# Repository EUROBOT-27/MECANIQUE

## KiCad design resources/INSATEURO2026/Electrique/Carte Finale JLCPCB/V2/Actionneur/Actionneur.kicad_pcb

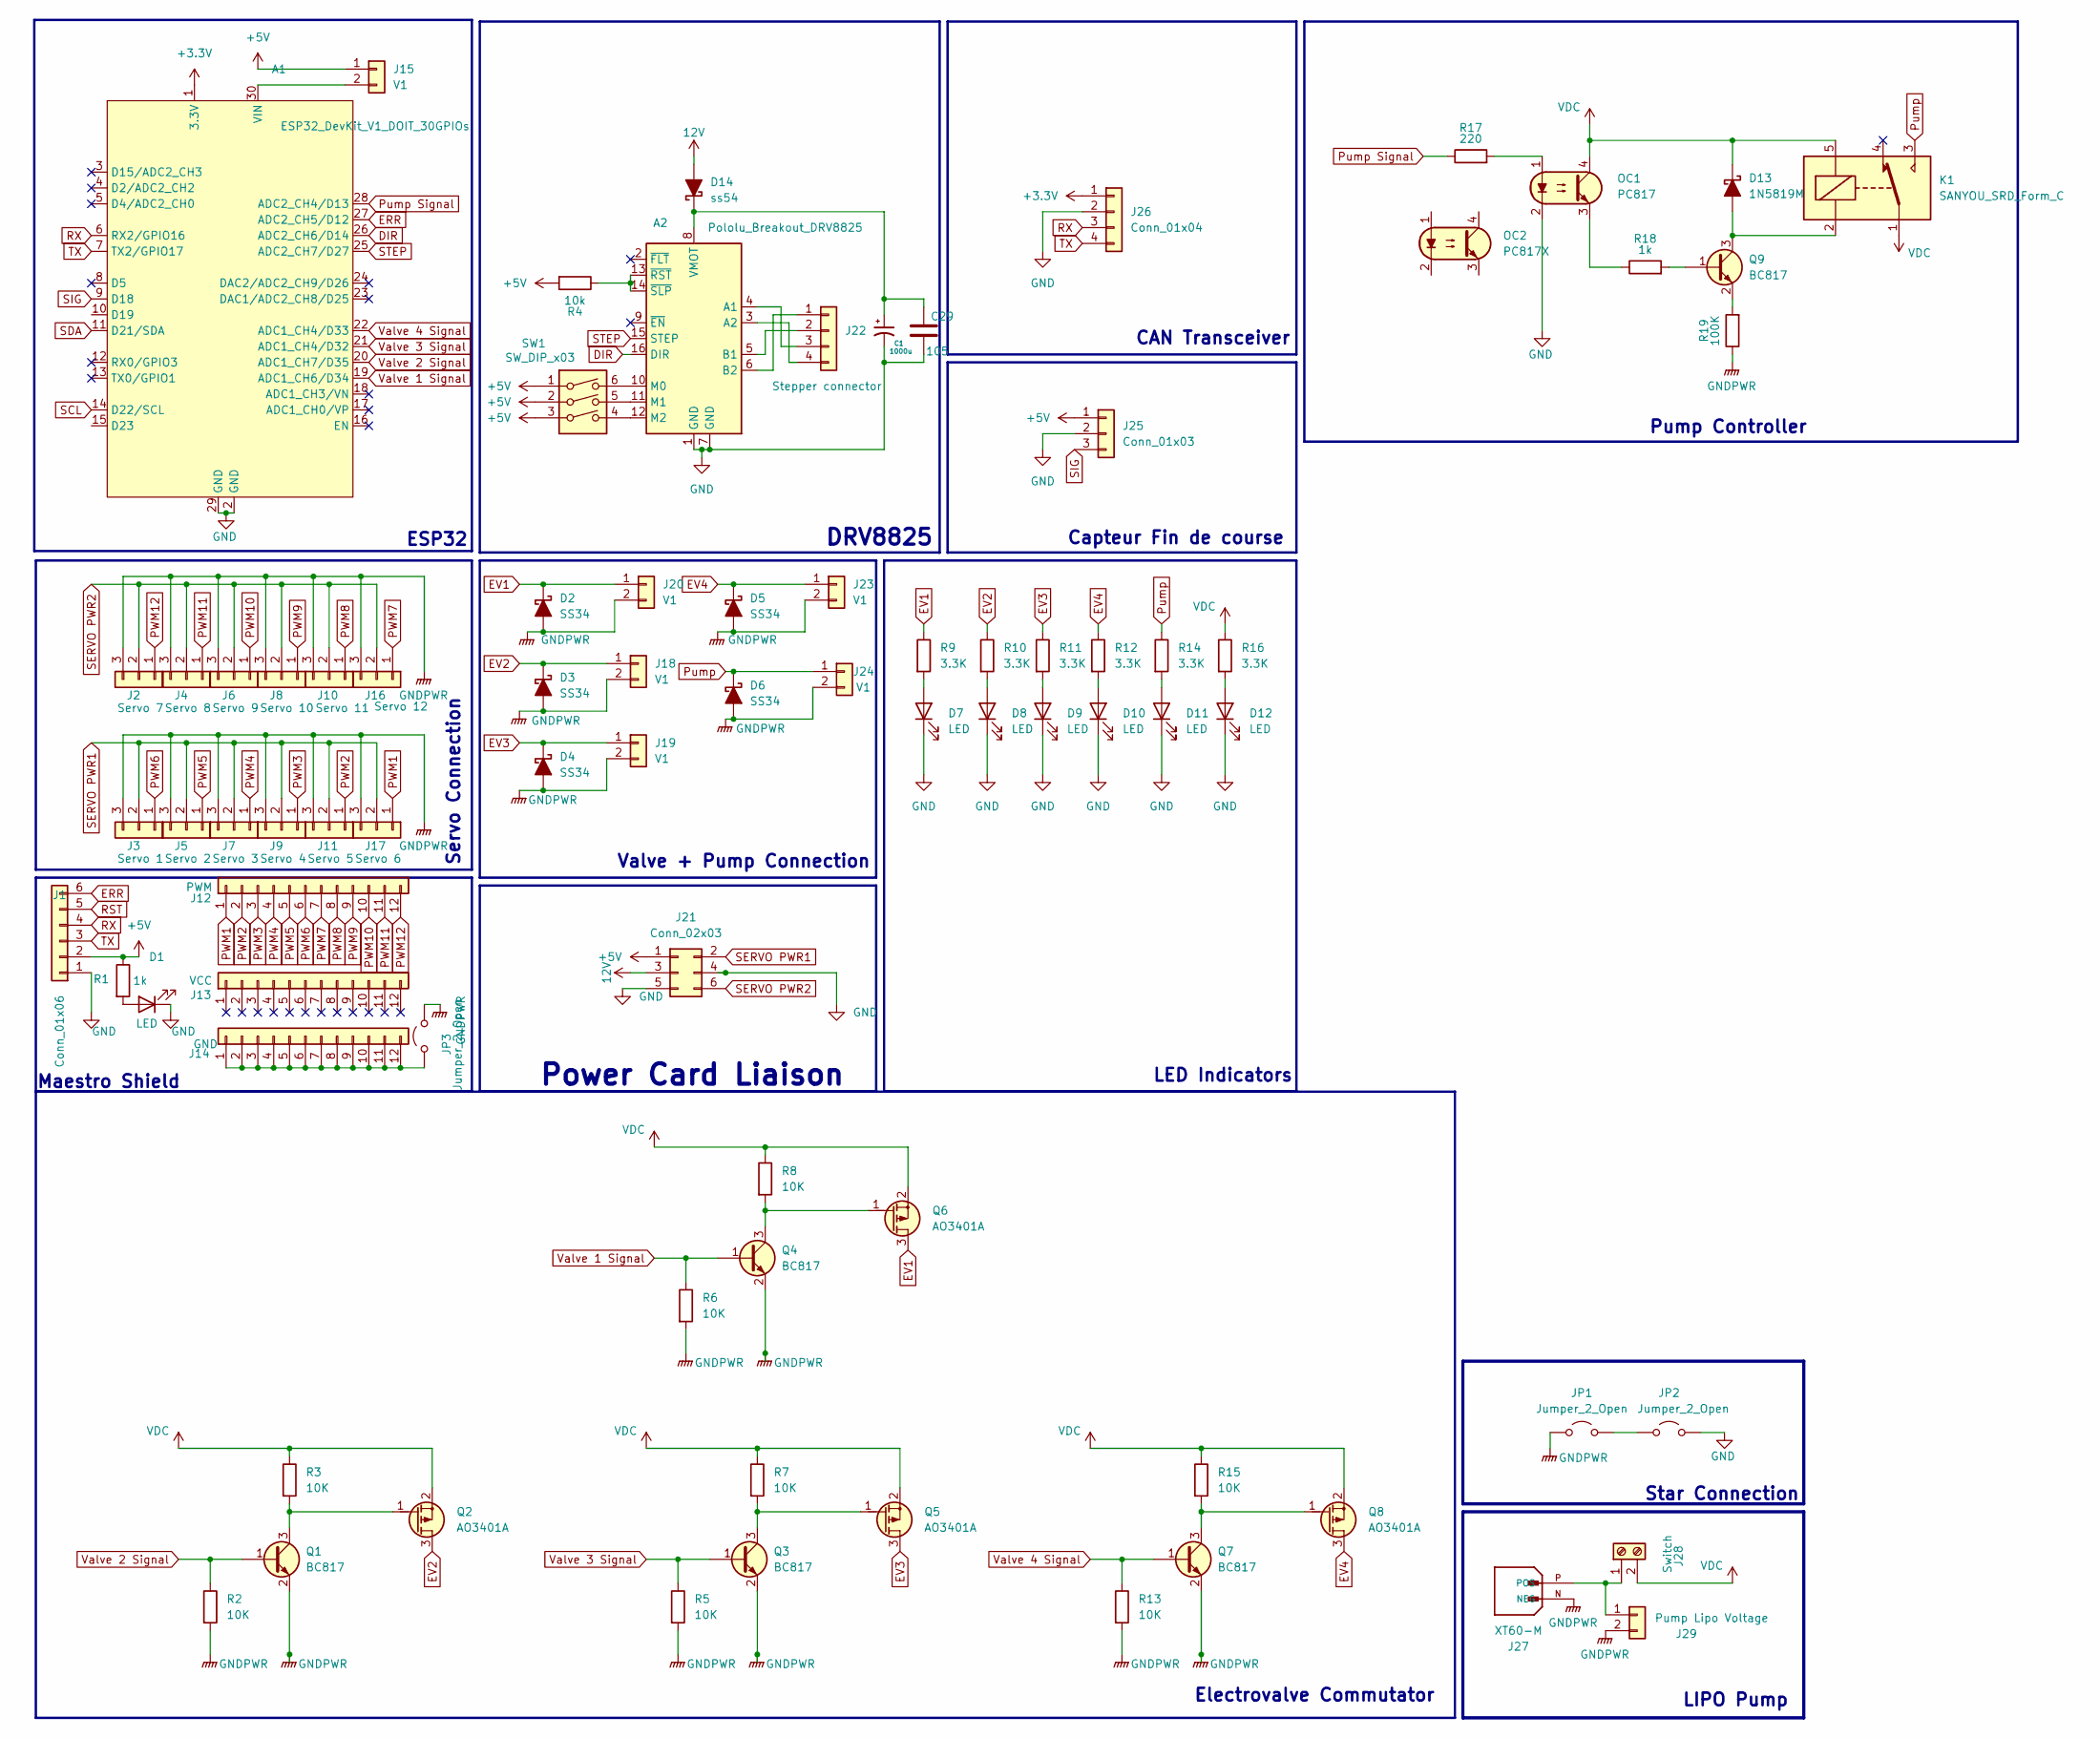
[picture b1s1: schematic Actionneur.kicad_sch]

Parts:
A1: ESP32_DevKit_V1_DOIT_30GPIOs; DOIT_ESP32_DEVKIT_30Pins
A2: Pololu_Breakout_DRV8825; Pololu_Breakout-16_15.2x20.3mm
C1: 1000u; CP_Elec_10x10.5
C29: 105; C_0603_1608Metric
D1, D7, D8, D9, D10, D11, D12: LED; LED_0603_1608Metric
D2, D3, D4, D5, D6: SS34; D_SOD-323
D13: 1N5819M; D_SMC
D14: ss54; D_SOD-323
J1: Conn_01x06; PinSocket_1x06_P2.54mm_Vertical
J2: Servo 7; PinHeader_1x03_P2.54mm_Vertical
J3: Servo 1; PinHeader_1x03_P2.54mm_Vertical
J4: Servo 8; PinHeader_1x03_P2.54mm_Vertical
J5: Servo 2; PinHeader_1x03_P2.54mm_Vertical
J6: Servo 9; PinHeader_1x03_P2.54mm_Vertical
J7: Servo 3; PinHeader_1x03_P2.54mm_Vertical
J8: Servo 10; PinHeader_1x03_P2.54mm_Vertical
J9: Servo 4; PinHeader_1x03_P2.54mm_Vertical
J10: Servo 11; PinHeader_1x03_P2.54mm_Vertical
J11: Servo 5; PinHeader_1x03_P2.54mm_Vertical
J12: PWM; PinSocket_1x12_P2.54mm_Vertical
J13: VCC; PinSocket_1x12_P2.54mm_Vertical
J14: GND; PinSocket_1x12_P2.54mm_Vertical
J15, J18, J19, J20, J23, J24: V1; JST_PH_B2B-PH-K_1x02_P2.00mm_Vertical
J16: Servo 12; PinHeader_1x03_P2.54mm_Vertical
J17: Servo 6; PinHeader_1x03_P2.54mm_Vertical
J21: Conn_02x03; Molex_Mini-Fit_Jr_5566-06A_2x03_P4.20mm_Vertical
J22: Stepper connector; JST_EH_B4B-EH-A_1x04_P2.50mm_Vertical
J25: Conn_01x03; JST_EH_B3B-EH-A_1x03_P2.50mm_Vertical
J26: Conn_01x04; JST_EH_B4B-EH-A_1x04_P2.50mm_Vertical
J27: XT60-M; AMASS_XT60-M; PARTREV V1.2
J28: Switch; TerminalBlock_Phoenix_MKDS-1,5-2-5.08_1x02_P5.08mm_Horizont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
J29: Pump Lipo Voltage; JST_PH_B2B-PH-K_1x02_P2.00mm_Vertical
JP1, JP2, JP3: Jumper_2_Open; Jumper_P2.54mm_D0.7mm
K1: SANYOU_SRD_Form_C; Relay_SPDT_SANYOU_SRD_Series_Form_C
OC1: PC817; Vishay_CNY64
OC2: PC817X; DIP-4_W7.62mm_LongPads
Q1, Q3, Q4, Q7, Q9: BC817; SOT-23
Q2, Q5, Q6, Q8: AO3401A; SOT-23
R1, R18: 1k; R_0603_1608Metric
R2, R3, R5, R6, R7, R8, R13, R15: 10K; R_0603_1608Metric
R4: 10k; R_0603_1608Metric
R9, R10, R11, R12, R14, R16: 3.3K; R_0603_1608Metric
R17: 220; R_0603_1608Metric
R19: 100K; R_0603_1608Metric
SW1: SW_DIP_x03; SW_DIP_SPSTx03_Slide_6.7x9.18mm_W6.73mm_P2.54mm_LowProfile_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

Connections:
12V: D14.2 (A), J21.3
+3.3V: A1.1 (3.3V), J26.1
+5V: J1.2, J15.1, J21.1, J25.1, R1.1, R4.2, SW1.1, SW1.2, SW1.3
Alt Pump: K1.4
DIR: A1.26 (ADC2_CH6/D14), A2.16 (DIR)
ERR: A1.27 (ADC2_CH5/D12), J1.6
EV1: D2.1 (K), J20.1, Q6.3 (D), R9.1
EV2: D3.1 (K), J18.1, Q2.3 (D), R10.1
EV3: D4.1 (K), J19.1, Q5.3 (D), R11.1
EV4: D5.1 (K), J23.1, Q8.3 (D), R12.1
GND: A1.2 (GND), A1.29 (GND), A2.1 (GND), A2.7 (GND), C1.2, C29.2, D1.1 (K), D7.1 (K), D8.1 (K), D9.1 (K), D10.1 (K), D11.1 (K), D12.1 (K), J1.1, J21.4, J21.5, J25.2, J26.2, JP2.2 (B), OC1.2
GNDPWR: D2.2 (A), D3.2 (A), D4.2 (A), D5.2 (A), D6.2 (A), J2.3, J3.3, J4.3, J5.3, J6.3, J7.3, J8.3, J9.3, J10.3, J11.3, J16.3, J17.3, J18.2, J19.2, J20.2, J23.2, J24.2, J27.N (NEG), J29.2, JP1.1 (A), JP3.2 (B), Q1.2 (E), Q3.2 (E), Q4.2 (E), Q7.2 (E), R2.2, R5.2, R6.2, R13.2, R19.1
unnamed: A1.30 (VIN), J15.2
unnamed: A2.4 (A1), J22.3
unnamed: A2.3 (A2), J22.4
unnamed: A2.5 (B1), J22.2
unnamed: A2.6 (B2), J22.1
unnamed: A2.10 (M0), SW1.6
unnamed: A2.11 (M1), SW1.5
unnamed: A2.12 (M2), SW1.4
unnamed: A2.8 (VMOT), C1.1, C29.1, D14.1 (K)
unnamed: A2.13 (~RST), A2.14 (~SLP), R4.1
unnamed: D1.2 (A), R1.2
unnamed: D7.2 (A), R9.2
unnamed: D8.2 (A), R10.2
unnamed: D9.2 (A), R11.2
unnamed: D10.2 (A), R12.2
unnamed: D11.2 (A), R14.2
unnamed: D12.2 (A), R16.2
unnamed: D13.2 (A), K1.2, Q9.3 (C)
unnamed: J14.1, J14.2, J14.3, J14.4, J14.5, J14.6, J14.7, J14.8, J14.9, J14.10, J14.11, J14.12, JP3.1 (A)
unnamed: J27.P (POS), J28.1, J29.1
unnamed: JP1.2 (B), JP2.1 (A)
unnamed: OC1.1, R17.2
unnamed: OC1.3, R18.1
unnamed: Q1.3 (C), Q2.1 (G), R3.2
unnamed: Q3.3 (C), Q5.1 (G), R7.2
unnamed: Q4.3 (C), Q6.1 (G), R8.2
unnamed: Q7.3 (C), Q8.1 (G), R15.2
unnamed: Q9.1 (B), R18.2
unnamed: Q9.2 (E), R19.2
PWM1: J12.1, J17.1
PWM2: J11.1, J12.2
PWM3: J9.1, J12.3
PWM4: J7.1, J12.4
PWM5: J5.1, J12.5
PWM6: J3.1, J12.6
PWM7: J12.7, J16.1
PWM8: J10.1, J12.8
PWM9: J8.1, J12.9
PWM10: J6.1, J12.10
PWM11: J4.1, J12.11
PWM12: J2.1, J12.12
Pump: D6.1 (K), J24.1, K1.3, R14.1
Pump Signal: A1.28 (ADC2_CH4/D13), R17.1
RST: J1.5
RX: A1.6 (RX2/GPIO16), J1.4, J26.3
SCL: A1.14 (D22/SCL)
SDA: A1.11 (D21/SDA)
SERVO PWR1: J3.2, J5.2, J7.2, J9.2, J11.2, J17.2, J21.2
SERVO PWR2: J2.2, J4.2, J6.2, J8.2, J10.2, J16.2, J21.6
SIG: A1.9 (D18), J25.3
STEP: A1.25 (ADC2_CH7/D27), A2.15 (STEP)
TX: A1.7 (TX2/GPIO17), J1.3, J26.4
VDC: D13.1 (K), J28.2, K1.1, K1.5, OC1.4, Q2.2 (S), Q5.2 (S), Q6.2 (S), Q8.2 (S), R3.1, R7.1, R8.1, R15.1, R16.1
Valve 1 Signal: A1.19 (ADC1_CH6/D34), Q4.1 (B), R6.1
Valve 2 Signal: A1.20 (ADC1_CH7/D35), Q1.1 (B), R2.1
Valve 3 Signal: A1.21 (ADC1_CH4/D32), Q3.1 (B), R5.1
Valve 4 Signal: A1.22 (ADC1_CH4/D33), Q7.1 (B), R13.1

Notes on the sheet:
LED Indicators
ESP32
LIPO Pump
Valve + Pump Connection
Star Connection
CAN Transceiver
Maestro Shield
Electrovalve Commutator
DRV8825
Pump Controller
Power Card Liaison
Servo Connection
Capteur Fin de course

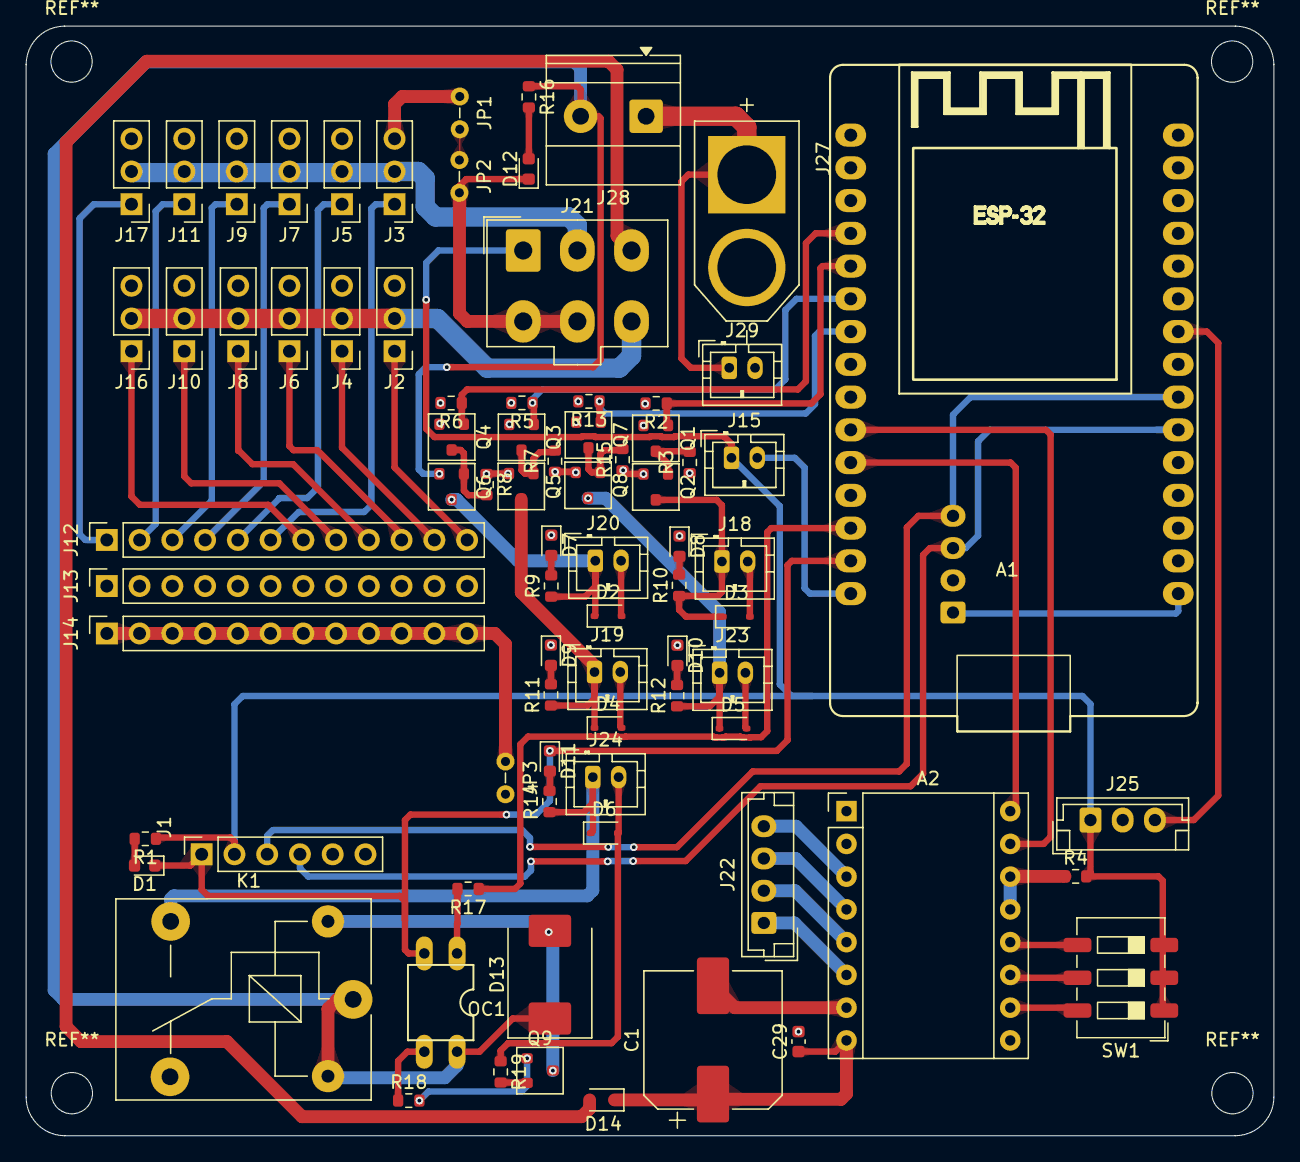
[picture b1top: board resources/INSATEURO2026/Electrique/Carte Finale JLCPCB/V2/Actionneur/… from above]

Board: 4 copper layers, 96.8 x 86.1 mm, 81 parts (1 on the bottom side), 65 nets.

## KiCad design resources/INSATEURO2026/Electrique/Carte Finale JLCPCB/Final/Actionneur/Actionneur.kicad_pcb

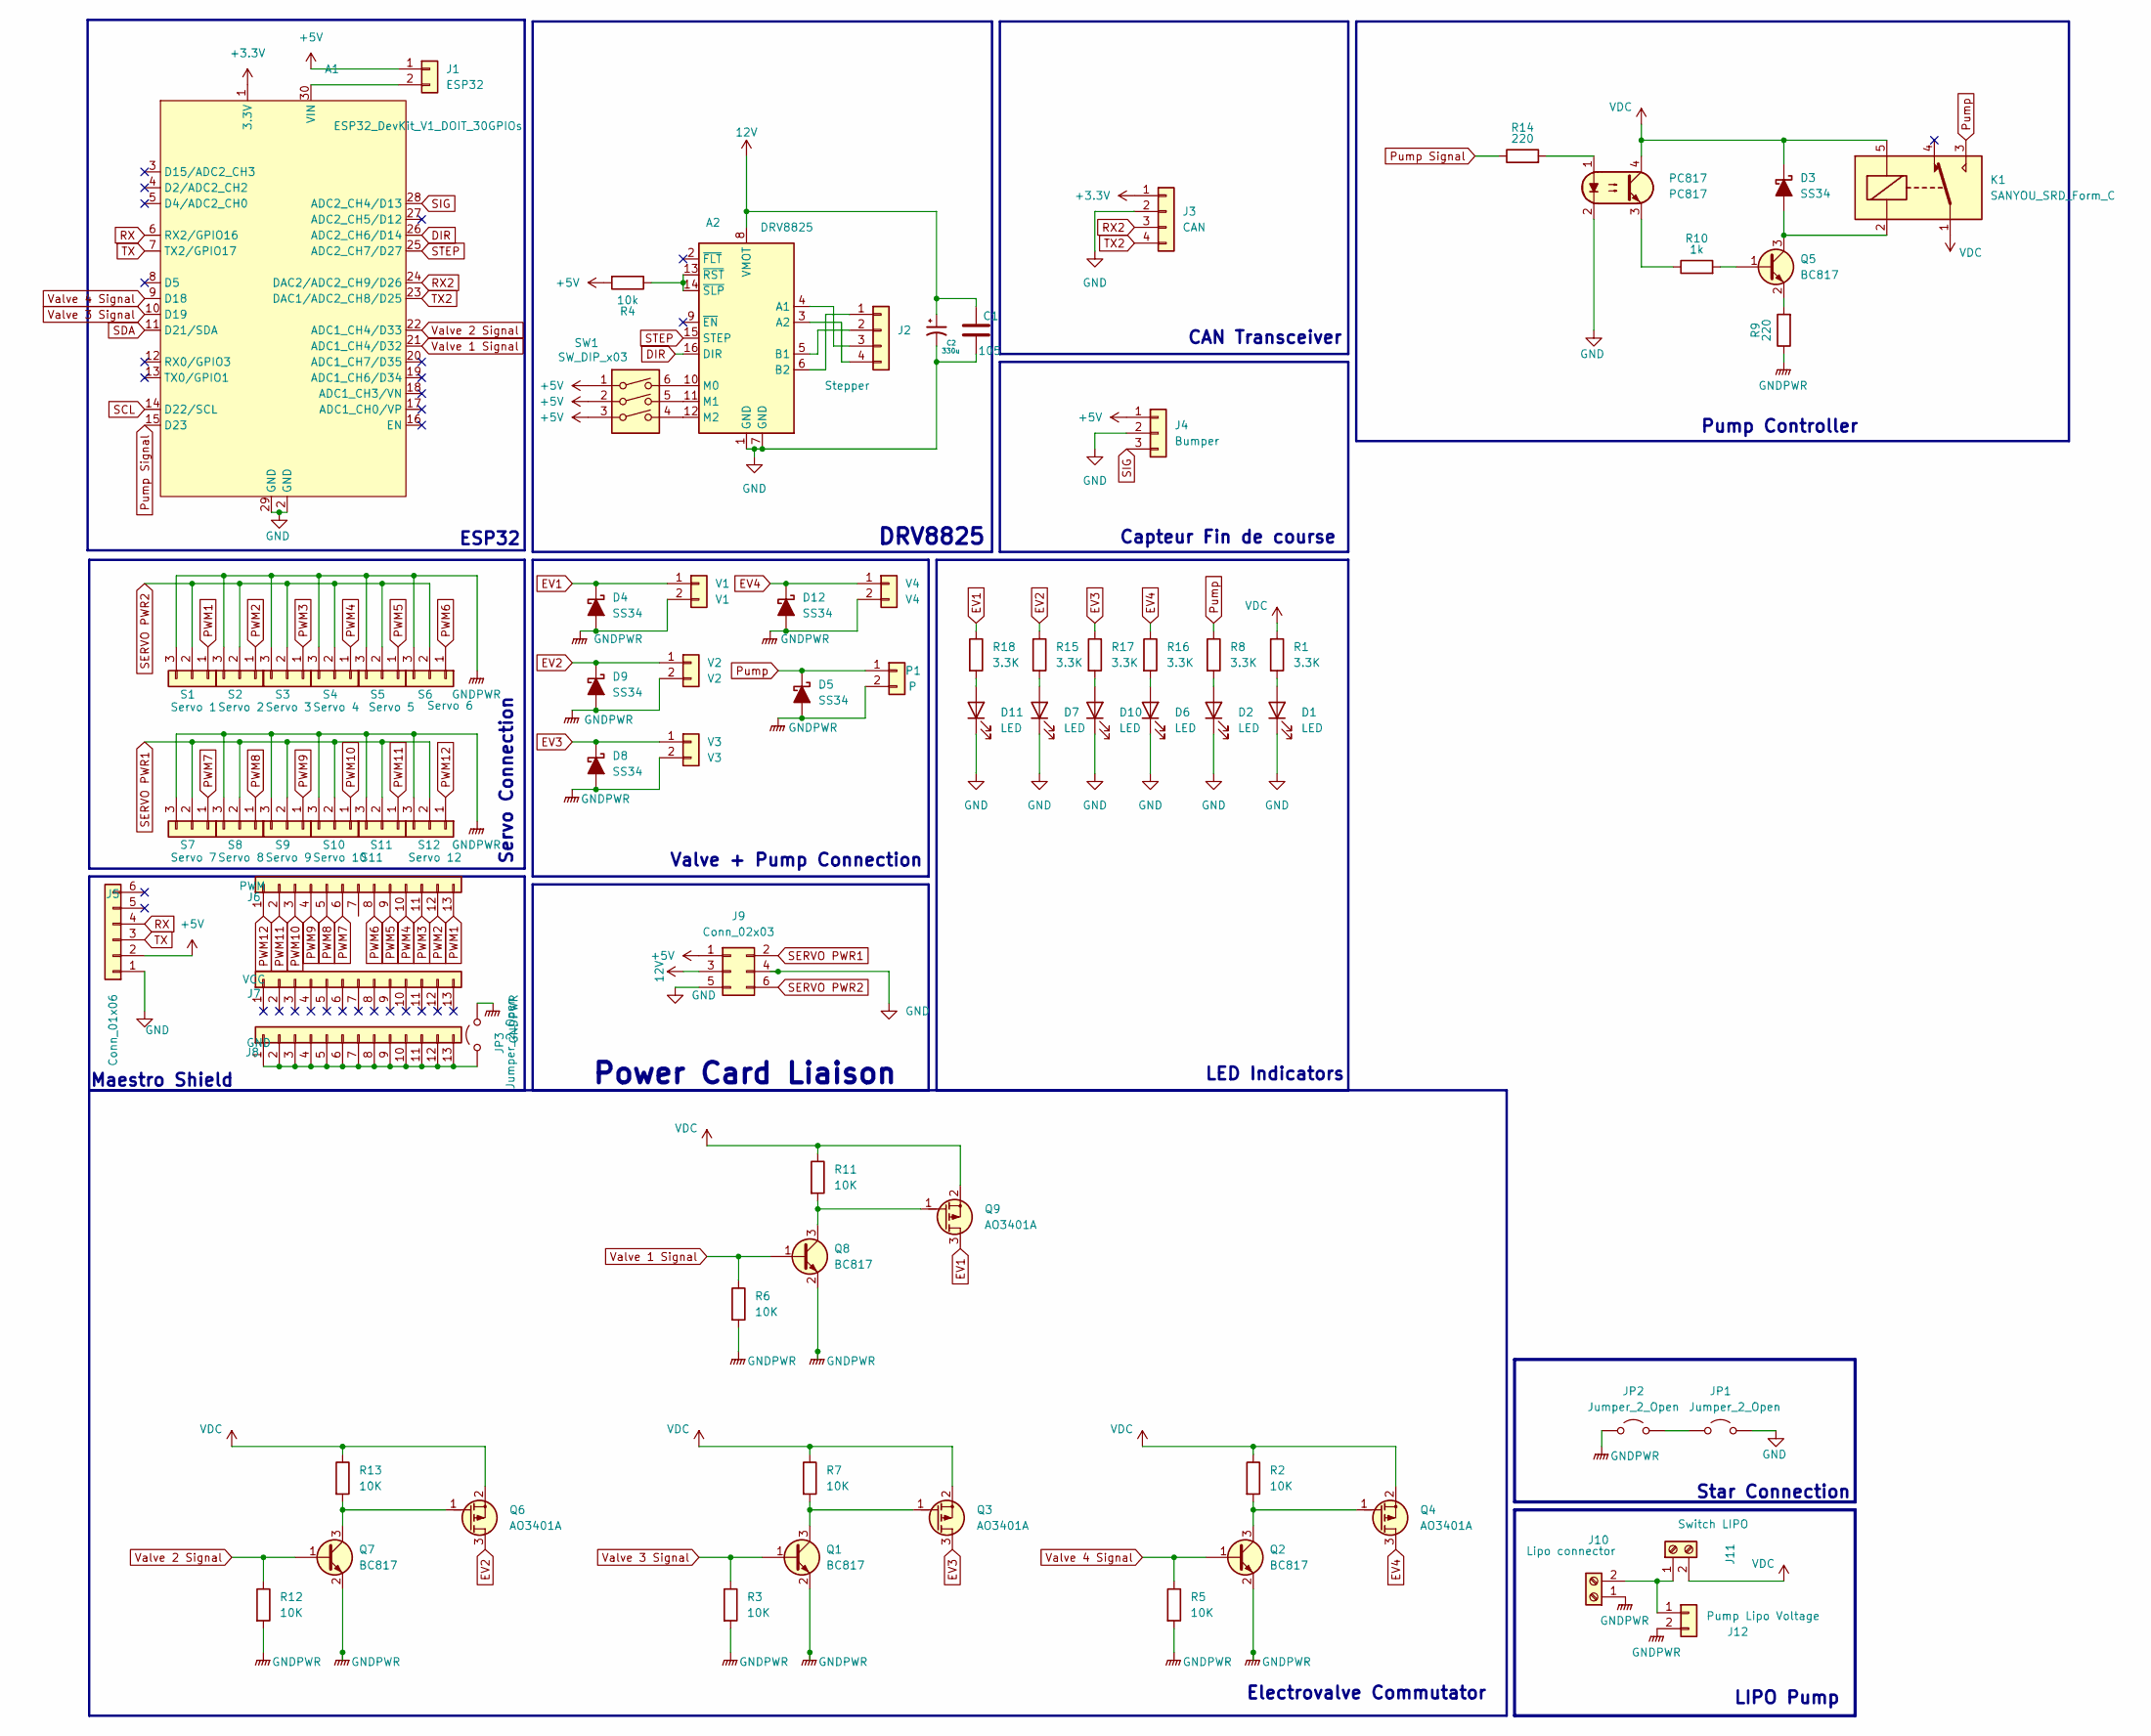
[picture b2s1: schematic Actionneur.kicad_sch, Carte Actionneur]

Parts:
A1: ESP32_DevKit_V1_DOIT_30GPIOs; DOIT_ESP32_DEVKIT_30Pins
A2: DRV8825; Pololu_Breakout-16_15.2x20.3mm
C1: 105; C_0603_1608Metric
C2: 330u; CP_Elec_10x10.5
D1, D2, D6, D7, D10, D11: LED; LED_0603_1608Metric
D3, D4, D5, D8, D9, D12: SS34; D_SOD-323
J1: ESP32; JST_XH_B2B-XH-A_1x02_P2.50mm_Vertical
J2: Stepper; JST_EH_B4B-EH-A_1x04_P2.50mm_Vertical
J3: CAN; JST_EH_B4B-EH-A_1x04_P2.50mm_Vertical
J4: Bumper; JST_EH_B3B-EH-A_1x03_P2.50mm_Vertical
J5: Conn_01x06; PinSocket_1x06_P2.54mm_Vertical
J6: PWM; PinSocket_1x13_P2.54mm_Vertical
J7: VCC; PinSocket_1x13_P2.54mm_Vertical
J8: GND; PinSocket_1x13_P2.54mm_Vertical
J9: Conn_02x03; Molex_Mini-Fit_Jr_5566-06A_2x03_P4.20mm_Vertical
J10: Lipo connector; TerminalBlock_Phoenix_MKDS-1,5-2-5.08_1x02_P5.08mm_Horizont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
J11: Switch LIPO; TerminalBlock_Phoenix_MKDS-1,5-2-5.08_1x02_P5.08mm_Horizont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
J12: Pump Lipo Voltage; JST_PH_B2B-PH-K_1x02_P2.00mm_Vertical
JP1, JP3: Jumper_2_Open; TestPoint_2Pads_Pitch2.54mm_Drill0.8mm
JP2: Jumper_2_Open; Jumper_P2.54mm_D0.7mm
K1: SANYOU_SRD_Form_C; Relay_SPDT_SANYOU_SRD_Series_Form_C
P1: P; JST_PH_B2B-PH-K_1x02_P2.00mm_Vertical
PC817: PC817; DIP-4_W7.62mm
Q1, Q2, Q5, Q7, Q8: BC817; SOT-23
Q3, Q4, Q6, Q9: AO3401A; SOT-23
R1, R8, R15, R16, R17, R18: 3.3K; R_0603_1608Metric
R2, R3, R5, R6, R7, R11, R12, R13: 10K; R_0603_1608Metric
R4: 10k; R_0603_1608Metric
R9, R14: 220; R_0603_1608Metric
R10: 1k; R_0603_1608Metric
S1: Servo 1; PinHeader_1x03_P2.54mm_Vertical
S2: Servo 2; PinHeader_1x03_P2.54mm_Vertical
S3: Servo 3; PinHeader_1x03_P2.54mm_Vertical
S4: Servo 4; PinHeader_1x03_P2.54mm_Vertical
S5: Servo 5; PinHeader_1x03_P2.54mm_Vertical
S6: Servo 6; PinHeader_1x03_P2.54mm_Vertical
S7: Servo 7; PinHeader_1x03_P2.54mm_Vertical
S8: Servo 8; PinHeader_1x03_P2.54mm_Vertical
S9: Servo 9; PinHeader_1x03_P2.54mm_Vertical
S10: Servo 10; PinHeader_1x03_P2.54mm_Vertical
S11: S11; PinHeader_1x03_P2.54mm_Vertical
S12: Servo 12; PinHeader_1x03_P2.54mm_Vertical
SW1: SW_DIP_x03; SW_DIP_SPSTx03_Slide_6.7x9.18mm_W6.73mm_P2.54mm_LowProfile_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
V1: V1; JST_PH_B2B-PH-K_1x02_P2.00mm_Vertical
V2: V2; JST_PH_B2B-PH-K_1x02_P2.00mm_Vertical
V3: V3; JST_PH_B2B-PH-K_1x02_P2.00mm_Vertical
V4: V4; JST_PH_B2B-PH-K_1x02_P2.00mm_Vertical

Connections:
12V: A2.8 (VMOT), C1.1, C2.1, J9.3
+3.3V: A1.1 (3.3V), J3.1
+5V: J1.1, J4.1, J5.2, J9.1, R4.2, SW1.1, SW1.2, SW1.3
DIR: A1.26 (ADC2_CH6/D14), A2.16 (DIR)
EV1: D4.1 (K), Q9.3 (D), R18.1, V1.1
EV2: D9.1 (K), Q6.3 (D), R15.1, V2.1
EV3: D8.1 (K), Q3.3 (D), R17.1, V3.1
EV4: D12.1 (K), Q4.3 (D), R16.1, V4.1
GND: A1.2 (GND), A1.29 (GND), A2.1 (GND), A2.7 (GND), C1.2, C2.2, D1.1 (K), D2.1 (K), D6.1 (K), D7.1 (K), D10.1 (K), D11.1 (K), J3.2, J4.2, J5.1, J9.4, J9.5, JP1.2 (B), PC817.2
GNDPWR: D4.2 (A), D5.2 (A), D8.2 (A), D9.2 (A), D12.2 (A), J10.1, J12.2, JP2.1 (A), JP3.2 (B), P1.2, Q1.2 (E), Q2.2 (E), Q7.2 (E), Q8.2 (E), R3.2, R5.2, R6.2, R9.1, R12.2, S1.3, S2.3, S3.3, S4.3, S5.3, S6.3, S7.3, S8.3, S9.3, S10.3, S11.3, S12.3, V1.2, V2.2, V3.2, V4.2
unnamed: A1.30 (VIN), J1.2
unnamed: A2.4 (A1), J2.3
unnamed: A2.3 (A2), J2.4
unnamed: A2.5 (B1), J2.2
unnamed: A2.6 (B2), J2.1
unnamed: A2.10 (M0), SW1.6
unnamed: A2.11 (M1), SW1.5
unnamed: A2.12 (M2), SW1.4
unnamed: A2.13 (~RST), A2.14 (~SLP), R4.1
unnamed: D1.2 (A), R1.2
unnamed: D2.2 (A), R8.2
unnamed: D3.2 (A), K1.2, Q5.3 (C)
unnamed: D6.2 (A), R16.2
unnamed: D7.2 (A), R15.2
unnamed: D10.2 (A), R17.2
unnamed: D11.2 (A), R18.2
unnamed: J8.1, J8.2, J8.3, J8.4, J8.5, J8.6, J8.7, J8.8, J8.9, J8.10, J8.11, J8.12, J8.13, JP3.1 (A)
unnamed: J10.2, J11.1, J12.1
unnamed: JP1.1 (A), JP2.2 (B)
unnamed: PC817.1, R14.2
unnamed: PC817.3, R10.1
unnamed: Q1.3 (C), Q3.1 (G), R7.2
unnamed: Q2.3 (C), Q4.1 (G), R2.2
unnamed: Q5.1 (B), R10.2
unnamed: Q5.2 (E), R9.2
unnamed: Q6.1 (G), Q7.3 (C), R13.2
unnamed: Q8.3 (C), Q9.1 (G), R11.2
PWM1: J6.13, S1.1
PWM2: J6.12, S2.1
PWM3: J6.11, S3.1
PWM4: J6.10, S4.1
PWM5: J6.9, S5.1
PWM6: J6.8, S6.1
PWM7: J6.6, S7.1
PWM8: J6.5, S8.1
PWM9: J6.4, S9.1
PWM10: J6.3, S10.1
PWM11: J6.2, S11.1
PWM12: J6.1, S12.1
Pump: D5.1 (K), K1.3, P1.1, R8.1
Pump Signal: A1.15 (D23), R14.1
RX: A1.6 (RX2/GPIO16), J5.4
RX2: A1.24 (DAC2/ADC2_CH9/D26), J3.3
SCL: A1.14 (D22/SCL)
SDA: A1.11 (D21/SDA)
SERVO PWR1: J9.2, S7.2, S8.2, S9.2, S10.2, S11.2, S12.2
SERVO PWR2: J9.6, S1.2, S2.2, S3.2, S4.2, S5.2, S6.2
SIG: A1.28 (ADC2_CH4/D13), J4.3
STEP: A1.25 (ADC2_CH7/D27), A2.15 (STEP)
TX: A1.7 (TX2/GPIO17), J5.3
TX2: A1.23 (DAC1/ADC2_CH8/D25), J3.4
VDC: D3.1 (K), J11.2, K1.1, K1.5, PC817.4, Q3.2 (S), Q4.2 (S), Q6.2 (S), Q9.2 (S), R1.1, R2.1, R7.1, R11.1, R13.1
Valve 1 Signal: A1.21 (ADC1_CH4/D32), Q8.1 (B), R6.1
Valve 2 Signal: A1.22 (ADC1_CH4/D33), Q7.1 (B), R12.1
Valve 3 Signal: A1.10 (D19), Q1.1 (B), R3.1
Valve 4 Signal: A1.9 (D18), Q2.1 (B), R5.1

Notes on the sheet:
LED Indicators
ESP32
LIPO Pump
Valve + Pump Connection
Star Connection
CAN Transceiver
Maestro Shield
Electrovalve Commutator
DRV8825
Pump Controller
Power Card Liaison
Servo Connection
Capteur Fin de course

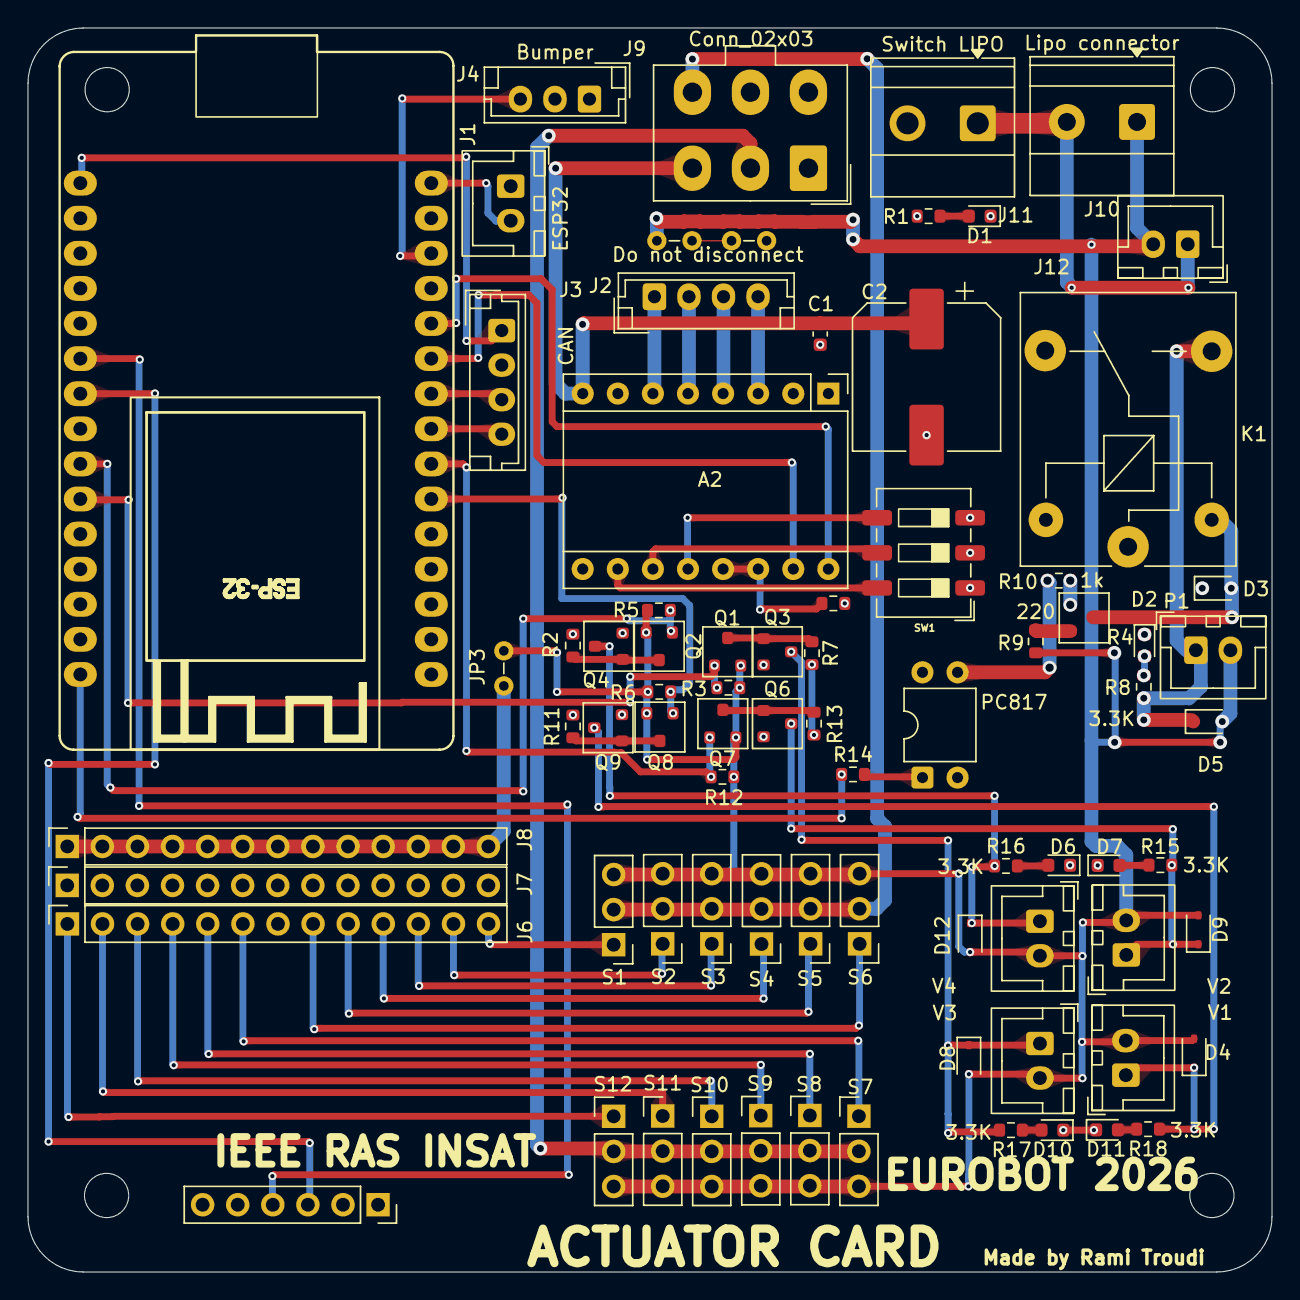
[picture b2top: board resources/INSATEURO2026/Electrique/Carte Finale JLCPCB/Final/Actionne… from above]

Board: 4 copper layers, 90.0 x 90.0 mm, 78 parts (0 on the bottom side), 64 nets.

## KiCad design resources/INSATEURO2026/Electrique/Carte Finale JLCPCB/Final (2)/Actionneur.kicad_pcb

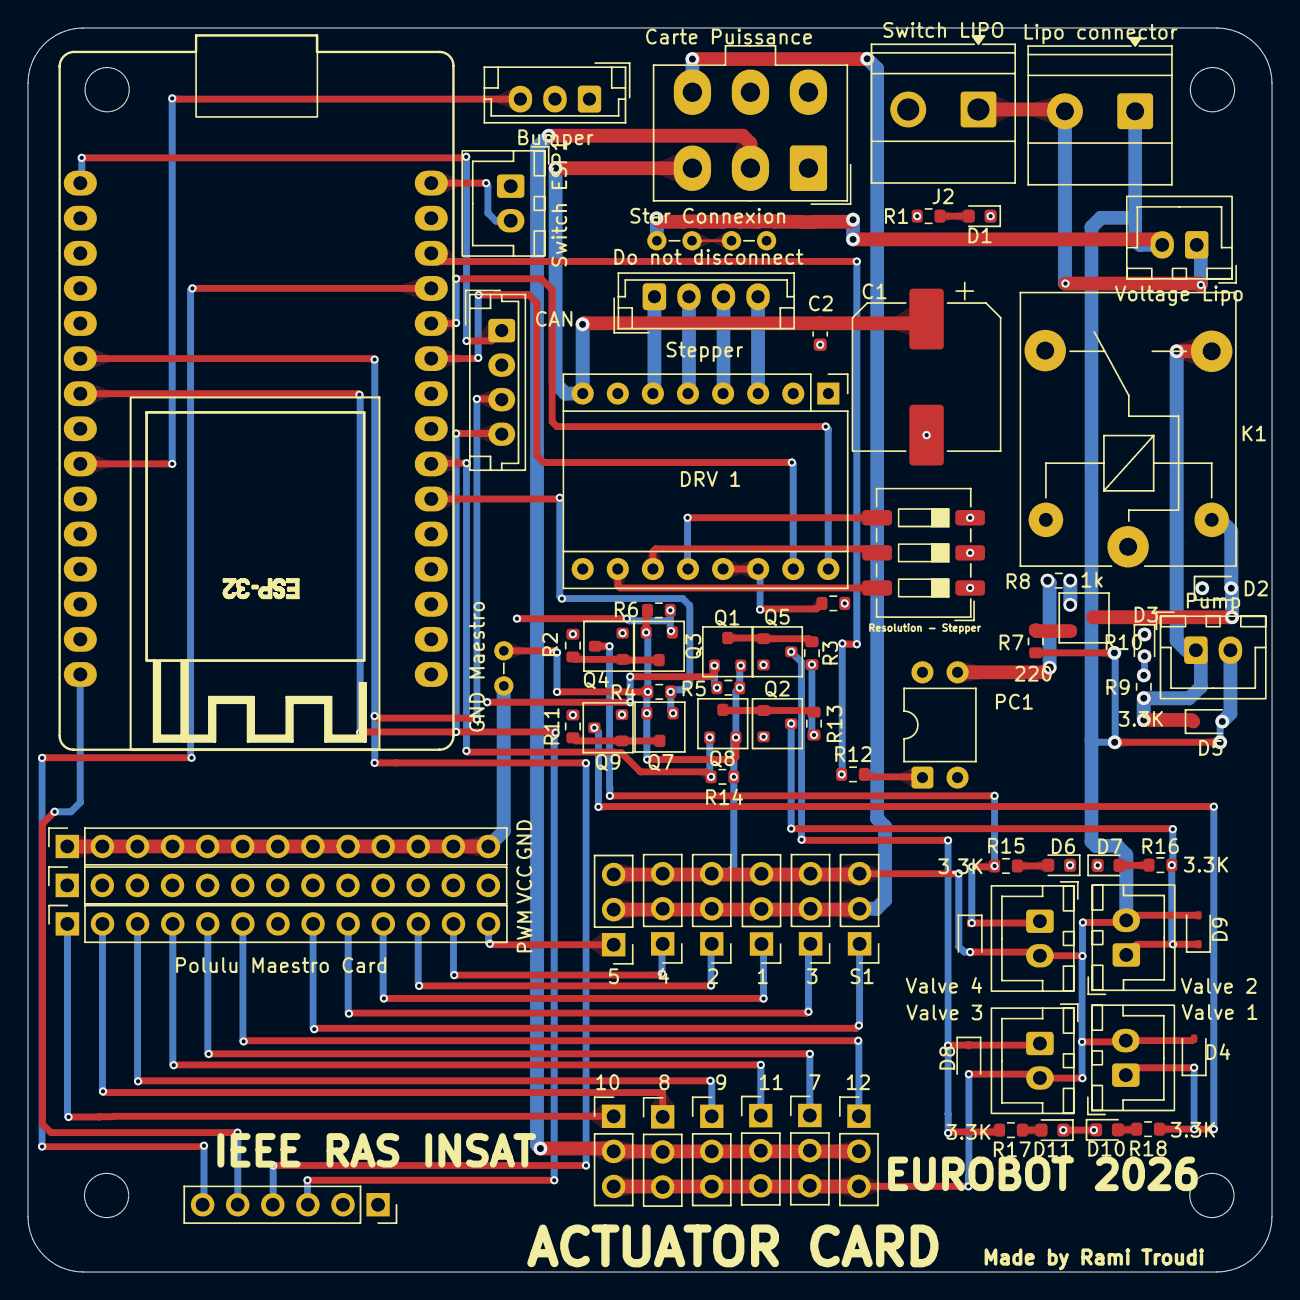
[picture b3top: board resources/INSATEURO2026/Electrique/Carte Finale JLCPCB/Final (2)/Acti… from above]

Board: 4 copper layers, 90.0 x 90.0 mm, 78 parts (0 on the bottom side), 64 nets.

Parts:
1: Servo 12; PinHeader_1x03_P2.54mm_Vertical
2: Servo 9; PinHeader_1x03_P2.54mm_Vertical
3: Servo 10; PinHeader_1x03_P2.54mm_Vertical
4: Servo 8; PinHeader_1x03_P2.54mm_Vertical
5: Servo 11; PinHeader_1x03_P2.54mm_Vertical
7: Servo 3; PinHeader_1x03_P2.54mm_Vertical
8: Servo 5; PinHeader_1x03_P2.54mm_Vertical
9: Servo 6; PinHeader_1x03_P2.54mm_Vertical
10: Servo 1; PinHeader_1x03_P2.54mm_Vertical
11: Servo 2; PinHeader_1x03_P2.54mm_Vertical
12: Servo 4; PinHeader_1x03_P2.54mm_Vertical
A1: ESP32_DevKit_V1_DOIT_30GPIOs; DOIT_ESP32_DEVKIT_30Pins
Bumper: Conn_01x03; JST_EH_B3B-EH-A_1x03_P2.50mm_Vertical
C1: 1000u; CP_Elec_10x10.5
C2: 105; C_0603_1608Metric
CAN: Conn_01x04; JST_EH_B4B-EH-A_1x04_P2.50mm_Vertical
Carte Puissance: Conn_02x03; Molex_Mini-Fit_Jr_5566-06A_2x03_P4.20mm_Vertical
D1, D3, D6, D7, D10, D11: LED; LED_0603_1608Metric
D2, D4, D5, D8, D9: SS34; D_SOD-323
DRV 1: Pololu_Breakout_DRV8825; Pololu_Breakout-16_15.2x20.3mm
GND: GND; PinSocket_1x13_P2.54mm_Vertical
GND Maestro: Jumper_2_Open; Jumper_P2.54mm_D0.7mm
J1: Lipo connector; TerminalBlock_Phoenix_MKDS-1,5-2-5.08_1x02_P5.08mm_Horizont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
J2: Switch LIPO; TerminalBlock_Phoenix_MKDS-1,5-2-5.08_1x02_P5.08mm_Horizont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
J3: Conn_01x06; PinSocket_1x06_P2.54mm_Vertical
JP1: Jumper_2_Open; Jumper_P2.54mm_D0.7mm
K1: SANYOU_SRD_Form_C; Relay_SPDT_SANYOU_SRD_Series_Form_C
PC1: PC817; DIP-4_W7.62mm
PWM: PWM; PinSocket_1x13_P2.54mm_Vertical
Polulu Maestro Card: SS34; D_SOD-323
Pump: V1; JST_XH_B2B-XH-A_1x02_P2.50mm_Vertical
Q1, Q3, Q6, Q7, Q8: BC817; SOT-23
Q2, Q4, Q5, Q9: AO3401A; SOT-23
R1, R9, R15, R16, R17, R18: 3.3K; R_0603_1608Metric
R2, R3, R4, R5, R6, R11, R13, R14: 10K; R_0603_1608Metric
R7, R12: 220; R_0603_1608Metric
R8: 1k; R_0603_1608Metric
R10: 10k; R_0603_1608Metric
Resolution - Stepper: SW_DIP_x03; SW_DIP_SPSTx03_Slide_6.7x9.18mm_W6.73mm_P2.54mm_LowProfile_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
S1: Servo 1; PinHeader_1x03_P2.54mm_Vertical
Star Connexion: Jumper_2_Open; Jumper_P2.54mm_D0.7mm
Stepper: Stepper connector; JST_EH_B4B-EH-A_1x04_P2.50mm_Vertical
Switch ESP1: V1; JST_XH_B2B-XH-A_1x02_P2.50mm_Vertical
VCC: VCC; PinSocket_1x13_P2.54mm_Vertical
Valve 1, Valve 2, Valve 3, Valve 4: V1; JST_XH_B2B-XH-A_1x02_P2.50mm_Vertical
Voltage Lipo: Pump Lipo Voltage; JST_XH_B2B-XH-A_1x02_P2.50mm_Vertical

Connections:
12V: C1.1, C2.1, Carte Puissance.3, DRV 1.8 (VMOT)
+3.3V: A1.1 (3.3V), CAN.1
+5V: Bumper.1, Carte Puissance.1, J3.2, R10.2, Resolution - Stepper.1, Resolution - Stepper.2, Resolution - Stepper.3
DIR: A1.26 (ADC2_CH6/D14), DRV 1.16 (DIR)
ERR: A1.27 (ADC2_CH5/D12), J3.6
EV1: D4.1 (K), Q9.3 (D), R18.1, Valve 1.1
EV2: D9.1 (K), Q2.3 (D), R16.1, Valve 2.1
EV3: D8.1 (K), Q5.3 (D), R17.1, Valve 3.1
EV4: Polulu Maestro Card.1 (K), Q4.3 (D), R15.1, Valve 4.1
GND: A1.2 (GND), A1.29 (GND), Bumper.2, C1.2, C2.2, CAN.2, Carte Puissance.4, Carte Puissance.5, D1.1 (K), D3.1 (K), D6.1 (K), D7.1 (K), D10.1 (K), D11.1 (K), DRV 1.1 (GND), DRV 1.7 (GND), J3.1, PC1.2, Star Connexion.2 (B)
GNDPWR: 1.3, 2.3, 3.3, 4.3, 5.3, 7.3, 8.3, 9.3, 10.3, 11.3, 12.3, D4.2 (A), D5.2 (A), D8.2 (A), D9.2 (A), GND Maestro.2 (B), J1.1, JP1.1 (A), Polulu Maestro Card.2 (A), Pump.2, Q1.2 (E), Q3.2 (E), Q7.2 (E), Q8.2 (E), R4.2, R5.2, R6.2, R7.1, R14.2, S1.3, Valve 1.2, Valve 2.2, Valve 3.2, Valve 4.2, Voltage Lipo.2
unnamed: A1.30 (VIN), Switch ESP1.2
unnamed: DRV 1.4 (A1), Stepper.3
unnamed: DRV 1.3 (A2), Stepper.4
unnamed: DRV 1.5 (B1), Stepper.2
unnamed: DRV 1.6 (B2), Stepper.1
unnamed: DRV 1.10 (M0), Resolution - Stepper.6
unnamed: DRV 1.11 (M1), Resolution - Stepper.5
unnamed: DRV 1.12 (M2), Resolution - Stepper.4
unnamed: DRV 1.13 (~RST), DRV 1.14 (~SLP), R10.1
unnamed: D2.2 (A), K1.2, Q6.3 (C)
unnamed: D10.2 (A), R18.2
unnamed: D7.2 (A), R16.2
unnamed: D11.2 (A), R17.2
unnamed: D6.2 (A), R15.2
unnamed: D3.2 (A), R9.2
unnamed: D1.2 (A), R1.2
unnamed: GND.1, GND.2, GND.3, GND.4, GND.5, GND.6, GND.7, GND.8, GND.9, GND.10, GND.11, GND.12, GND.13, GND Maestro.1 (A)
unnamed: J1.J27 (Pin_2), J2.1, Voltage Lipo.1
unnamed: JP1.2 (B), Star Connexion.1 (A)
unnamed: PC1.1, R12.2
unnamed: PC1.3, R8.1
unnamed: Q2.1 (G), Q8.3 (C), R13.2
unnamed: Q1.3 (C), Q5.1 (G), R3.2
unnamed: Q7.3 (C), Q9.1 (G), R11.2
unnamed: Q3.3 (C), Q4.1 (G), R2.2
unnamed: Q6.1 (B), R8.2
unnamed: Q6.2 (E), R7.2
PWM1: PWM.13, S1.1
PWM2: 4.1, PWM.12
PWM3: 2.1, PWM.11
PWM4: 3.1, PWM.10
PWM5: 5.1, PWM.9
PWM6: 1.1, PWM.8
PWM7: 10.1, PWM.6
PWM8: 11.1, PWM.5
PWM9: 7.1, PWM.4
PWM10: 12.1, PWM.3
PWM11: 8.1, PWM.2
PWM12: 9.1, PWM.1
Pump: D5.1 (K), K1.3, Pump.1, R9.1
Pump Signal: A1.28 (ADC2_CH4/D13), R12.1
RST: A1.15 (D23), J3.5
RX: A1.6 (RX2/GPIO16), CAN.3, J3.4
SERVO PWR1: 7.2, 8.2, 9.2, 10.2, 11.2, 12.2, Carte Puissance.2
SERVO PWR2: 1.2, 2.2, 3.2, 4.2, 5.2, Carte Puissance.6, S1.2
SIG: A1.9 (D18), Bumper.3
STEP: A1.25 (ADC2_CH7/D27), DRV 1.15 (STEP)
TX: A1.7 (TX2/GPIO17), CAN.4, J3.3
VDC: D2.1 (K), J2.2, K1.1, K1.5, PC1.4, Q2.2 (S), Q4.2 (S), Q5.2 (S), Q9.2 (S), R1.1, R2.1, R3.1, R11.1, R13.1
Valve 1 Signal: A1.21 (ADC1_CH4/D32), Q7.1 (B), R4.1
Valve 2 Signal: A1.22 (ADC1_CH4/D33), Q8.1 (B), R14.1
Valve 3 Signal: A1.23 (DAC1/ADC2_CH8/D25), Q1.1 (B), R5.1
Valve 4 Signal: A1.24 (DAC2/ADC2_CH9/D26), Q3.1 (B), R6.1
